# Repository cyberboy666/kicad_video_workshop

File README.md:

# kicad_video_workshop

an interactive kicad workshop for diy video-art making instruments

## getting started:

- download [kicad](https://kicad-pcb.org/download/) ( version >=5 )
- download _this_ repo (git clone or as zip under _code_ here)
- open the file in _workshop_project_ / __workshop_project.pro__ with kicad

## the challenge:

together we will try to adapt a video glitch processing circuit created orginally by [Karl Klomp](https://www.karlklomp.nl/) known as __the rupter__. this project and many other interesting historic video hardware glitch machines can be seen on [web-archive](https://web.archive.org/web/20150206171254/https://www.karlklomp.nl/) of their site.

<details>
<summary>details of the original circuit</summary>

### original circuit:

### my interpretation:

- [video demo](https://videos.scanlines.xyz/videos/watch/c60b0d9a-0be3-4889-8f0d-863ae294ad4a)

there are a few quirks of this design that make it difficult to adapt to a pcb project:

- its not clear which pot values to use - 100k or 1k ? (100ohm pots are bery uncommon) after testing i liked the effects with 1k_pots better
- although possible to use a rotary switch on pcb, the footprints for these are a little complicated and i opted to use some (cheap) slide switches in parallel instead. lower resistor values seemed to work better here than higher ones. you should experiment for yourself which values to use here !
- a 'circuit bent' style schematic can be difficult to understand since often are based on misusing components. Bastien made a [simulation](https://tinyurl.com/yyvfhpfx) of the first stage which doesnt appear to do much in theory. as is often the case things will be different in practice. 

### further notes on the circuit

from building:

- tried skipping the power regulator part and going 5v straight into the ic -> seems to work quite well 
- [lm317](http://www.learningaboutelectronics.com/Articles/LM317-voltage-regulator) is adjustable voltage regulator - ouput voltage is `1.25*(1 + r2/r1)` where in this case r2=1k and r1=220ohm. so voltage output should be around 7v. confirmed this when building
- i measured the current from the lm317 and was around 20mA so could also use the smaller/cheaper [part](https://www.taydaelectronics.com/lm317lz-lm317l-lm317-0-1a-voltage-regulator-ic.html)
- tried with 200ohm , 1k and 100k pots. all were quite interesting. i would choose 1k pots myself.
- tried with some different cap values. no cap connected gives closer to a clean signal. higher caps tend to just give dropouts (with a few hard to tune effects) lower values seems most interesting. i would experiment some more with which cap values to use.
- i tried to figure out which way to orieintate the pots to make most sense. still it is not that obvious to me. would have to play around with the circuit some more to fine tune this.
- i tried switching -in/out of second opamp to see if liked the effect better but it wasnt as interesting.
- i tested with ntsc and it seems to give better colour glitches than as i remember with pal

</details>

## the schematic

here is a handdrawn schematic of my interpretation which we will try to create in kicad:

## some kicad shortcuts

Schematics shortcuts:

- __a__ to add symbol
- __m__ to move symbol
- __e__ to edit symbol
- __c__ to duplicate symbol
- __w__ to draw wire
- _esc_ to return to pointer tool

pcb_route shortcuts:

- __m__ to move item
- __x__ to route track
- __v__ to add via
- _esc_ to return to pointer tool

## links to parts used:

part | footprint | link
--- | --- | ---
rca_jack | - | [mouser](https://www.mouser.de/ProductDetail/CUI-Devices/RCJ-024?qs=%2Fha2pyFaduhcVxkiXFV6ZkU5qdMo9ssjy3LnObhig%2FI%3D), [ali](https://www.aliexpress.com/item/32851836707.html)
spdt_slide_switch | - | [tayda](https://www.taydaelectronics.com/slide-switch-1p2t-through-hole-0-3a-30vdc.html)
spdt_toggle_switch | - | [tayda](https://www.taydaelectronics.com/mini-toggle-switch-spdt-on-none-on.html)
dpst_slide_switch | - | [tayda](https://www.taydaelectronics.com/slide-switch-dpdt-solder-lug-3a-250vac.html)
dpst_toggle_switch | - | [tayda](https://www.taydaelectronics.com/mini-toggle-switch-dpdt-on-on.html)
ad8072 | - | [mouser_dip](https://www.mouser.de/ProductDetail/Analog-Devices/AD8072JNZ?qs=%2FtpEQrCGXCyHkd%2F8k%2FoSBQ%3D%3D)
1k_pot | - | [tayda](https://www.taydaelectronics.com/1k-ohm-linear-taper-potentiometer-round-knurled-plastic-shaft-pcb-9mm.html), [mouser](https://www.mouser.de/ProductDetail/Bourns/PTV09A-4225F-B102?qs=Qzws7J6gxqyeFhc0kO3Q7A%3D%3D)
7pst_rotary_switch | none | [tayda](https://www.taydaelectronics.com/rotary-switch-1-pole-7-position-alpha-sr2511-3599.html), [mouser](https://www.mouser.de/ProductDetail/Alpha-Taiwan/SR2511F-0107-19R0B-E9-S-W-159?qs=8%252Br4Hz5Xir%2FR%2FBhSWT66hw%3D%3D)

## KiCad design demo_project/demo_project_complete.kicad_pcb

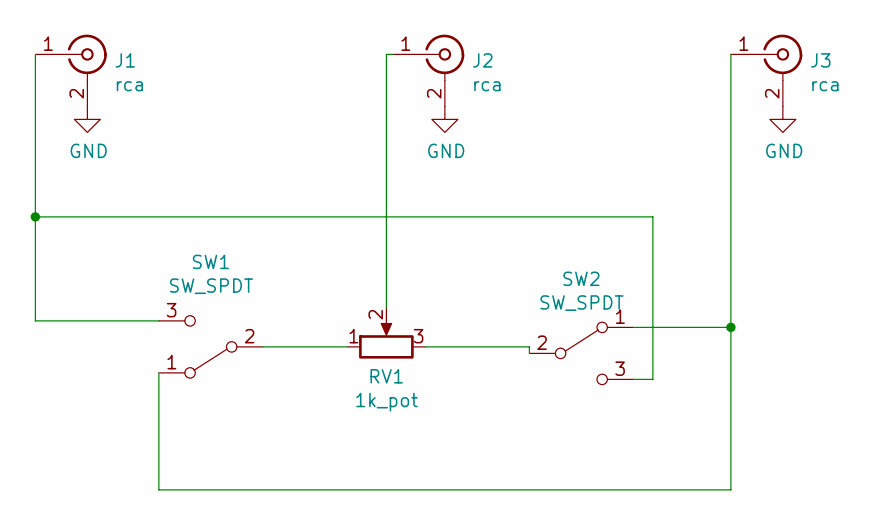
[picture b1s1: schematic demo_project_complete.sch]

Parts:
J1, J2, J3: rca; rca_vertical
RV1: 1k_pot; pot_vertical_9mm
SW1, SW2: SW_SPDT; spdt_slide_switch_small_tayda

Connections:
GND: J1.2 (Ext), J2.2 (Ext), J3.2 (Ext)
unnamed: J1.1 (In), SW1.3 (C), SW2.3 (C)
unnamed: J2.1 (In), RV1.2
unnamed: J3.1 (In), SW1.1 (A), SW2.1 (A)
unnamed: RV1.1, SW1.2 (B)
unnamed: RV1.3, SW2.2 (B)

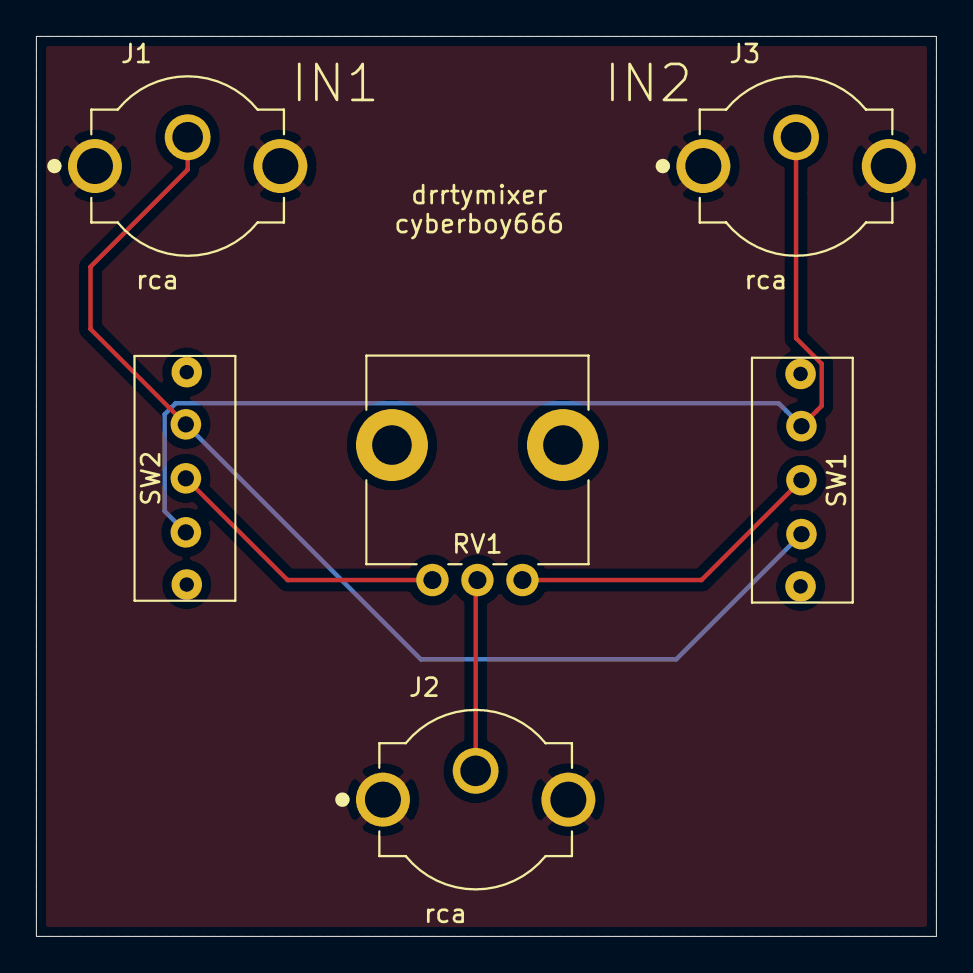
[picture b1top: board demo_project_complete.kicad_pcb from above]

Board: 2 copper layers, 50.0 x 50.0 mm, 6 parts (0 on the bottom side), 6 nets.

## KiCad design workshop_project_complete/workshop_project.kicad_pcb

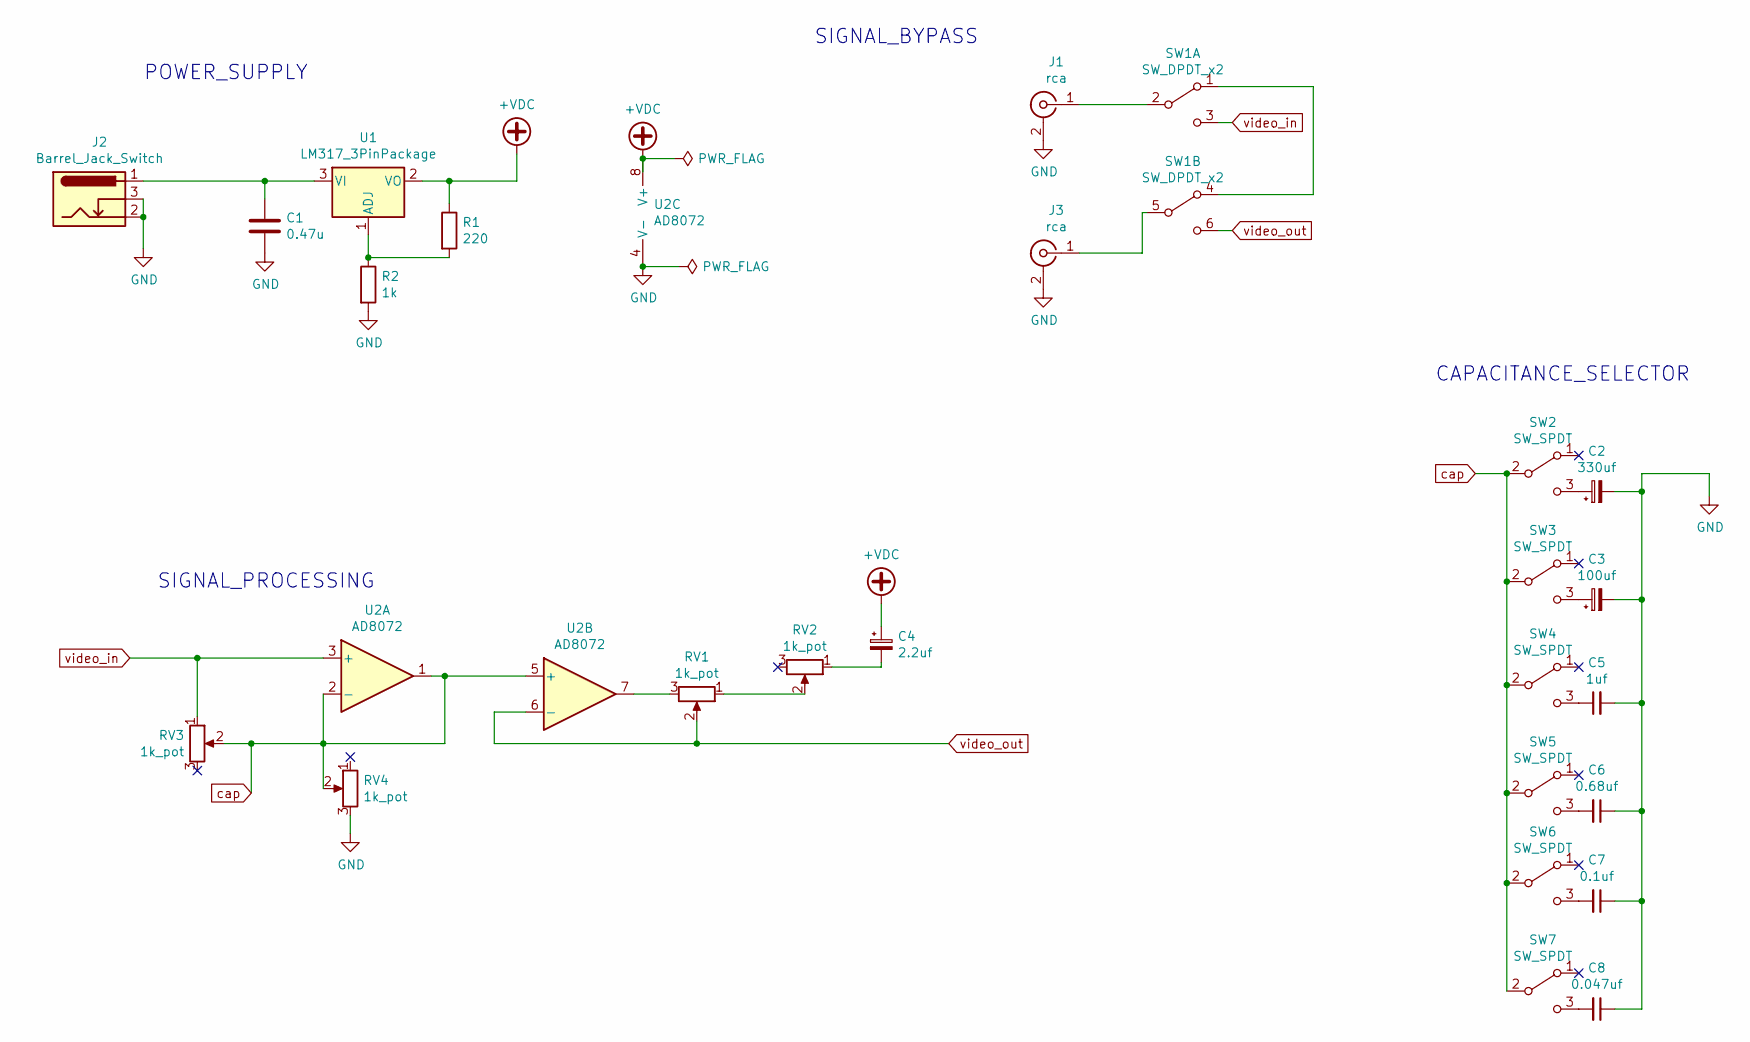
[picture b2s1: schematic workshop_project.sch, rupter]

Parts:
C1: 0.47u; CP_Radial_D5.0mm_P2.50mm
C2: 330uf; CP_Radial_D5.0mm_P2.50mm
C3: 100uf; CP_Radial_D5.0mm_P2.50mm
C4: 2.2uf; CP_Radial_D5.0mm_P2.50mm
C5: 1uf; C_Disc_D4.7mm_W2.5mm_P5.00mm
C6: 0.68uf; C_Disc_D4.7mm_W2.5mm_P5.00mm
C7: 0.1uf; C_Disc_D4.7mm_W2.5mm_P5.00mm
C8: 0.047uf; C_Disc_D4.7mm_W2.5mm_P5.00mm
J1, J3: rca; rca_vertical
J2: Barrel_Jack_Switch; BarrelJack_Horizontal
R1: 220; R_Axial_DIN0204_L3.6mm_D1.6mm_P5.08mm_Horizontal
R2: 1k; R_Axial_DIN0204_L3.6mm_D1.6mm_P5.08mm_Horizontal
RV1, RV2, RV3, RV4: 1k_pot; pot_vertical_9mm
SW1: SW_DPDT_x2; dpdt_mini_toggle_switch_tayda
SW2, SW3, SW4, SW5, SW6, SW7: SW_SPDT; spdt_slide_switch_small_tayda
U1: LM317_3PinPackage; TO-92L_HandSolder
U2: AD8072; DIP-8_W7.62mm_LongPads

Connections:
+VDC: C4.1, R1.1, U1.2 (VO), U2.8 (V+)
GND: C1.2, C2.2, C3.2, C5.2, C6.1, C7.1, C8.1, J1.2 (Ext), J2.2, J2.3, J3.2 (Ext), R2.2, RV4.3, U2.4 (V-)
unnamed: C1.1, J2.1, U1.3 (VI)
unnamed: C2.1, SW2.3 (C)
unnamed: C3.1, SW3.3 (C)
unnamed: C4.2, RV2.1
unnamed: C5.1, SW4.3 (C)
unnamed: C6.2, SW5.3 (C)
unnamed: C7.2, SW6.3 (C)
unnamed: C8.2, SW7.3 (C)
unnamed: J1.1 (In), SW1.2 (B)
unnamed: J3.1 (In), SW1.5 (B)
unnamed: R1.2, R2.1, U1.1 (ADJ)
unnamed: RV1.1, RV2.2
unnamed: RV1.3, U2.7
unnamed: SW1.1 (A), SW1.4 (A)
cap: RV3.2, RV4.2, SW2.2 (B), SW3.2 (B), SW4.2 (B), SW5.2 (B), SW6.2 (B), SW7.2 (B), U2.1, U2.2 (-), U2.5 (+)
video_in: RV3.1, SW1.3 (C), U2.3 (+)
video_out: RV1.2, SW1.6 (C), U2.6 (-)

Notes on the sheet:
POWER_SUPPLY
SIGNAL_PROCESSING
SIGNAL_BYPASS
CAPACITANCE_SELECTOR

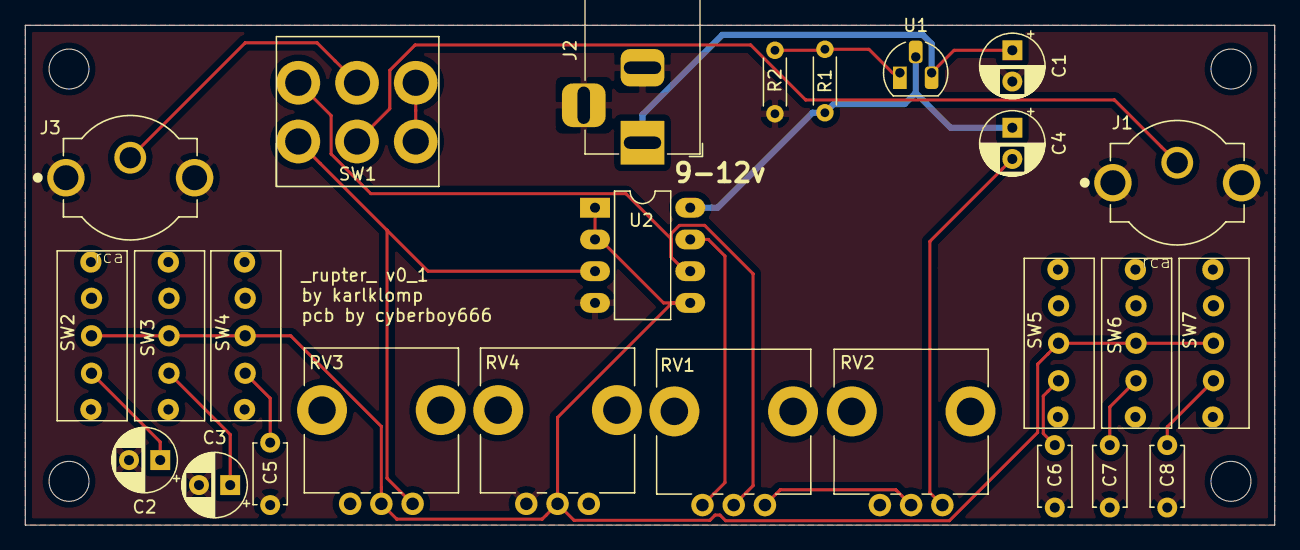
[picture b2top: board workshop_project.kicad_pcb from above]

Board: 2 copper layers, 100.0 x 40.0 mm, 26 parts (0 on the bottom side), 19 nets.

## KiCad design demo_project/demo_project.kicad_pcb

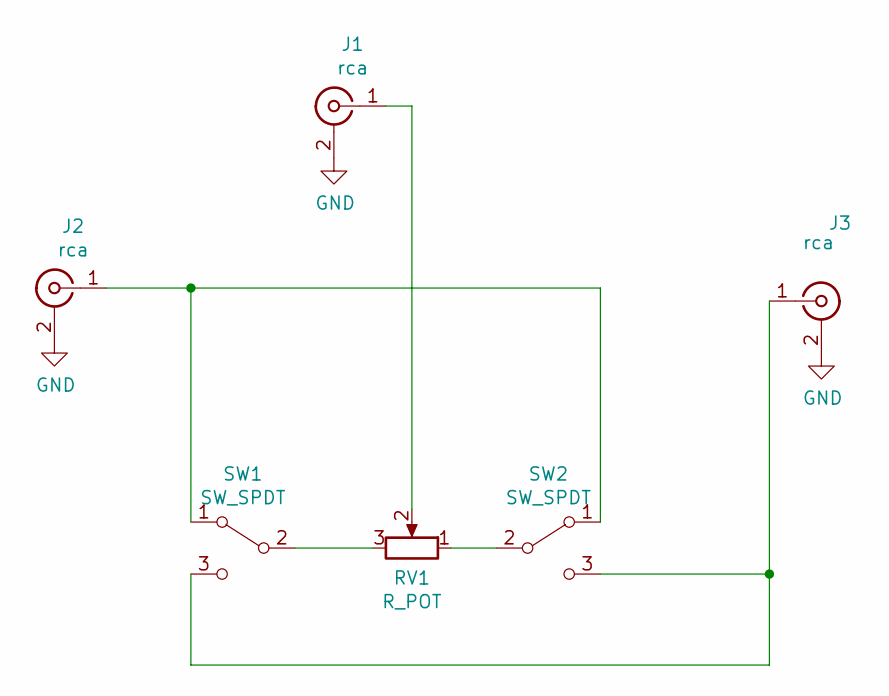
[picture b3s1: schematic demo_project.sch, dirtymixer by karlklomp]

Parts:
J1, J2, J3: rca; rca_vertical
RV1: R_POT; pot_vertical_9mm
SW1, SW2: SW_SPDT; spdt_mini_toggle_switch_tayda

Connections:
GND: J1.2 (Ext), J2.2 (Ext), J3.2 (Ext)
unnamed: J1.1 (In), RV1.2
unnamed: J2.1 (In), SW1.1 (A), SW2.1 (A)
unnamed: J3.1 (In), SW1.3 (C), SW2.3 (C)
unnamed: RV1.1, SW2.2 (B)
unnamed: RV1.3, SW1.2 (B)

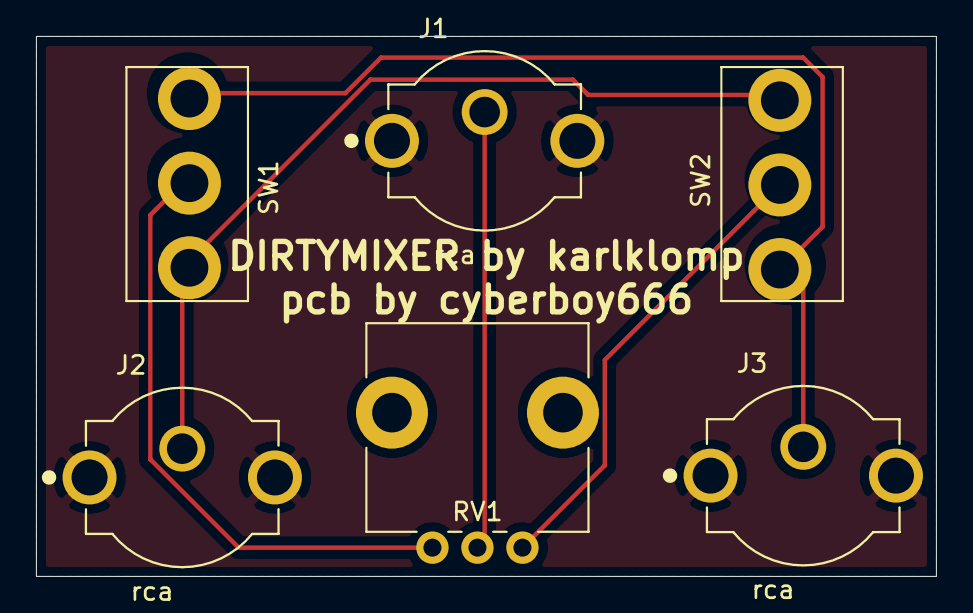
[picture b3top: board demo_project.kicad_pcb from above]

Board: 2 copper layers, 50.0 x 30.0 mm, 6 parts (0 on the bottom side), 6 nets.

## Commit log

2020-10-27 adding files for the workshop
2020-10-28 added complete examples
2020-11-02 update workshop complete
2020-11-15 link fb lib
2021-07-19 small update
